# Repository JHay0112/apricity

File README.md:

# Apricity - Sunrise Alarm

Apricity is my second attempt at designing and building a sunrise alarm. 

The first attempt (https://jordanhay.com/blog/2021/08/sunrise-alarm) was based upon a development board and a 3D printed enclosure. Apricity will improve upon this design with a custom PCB and firmware.

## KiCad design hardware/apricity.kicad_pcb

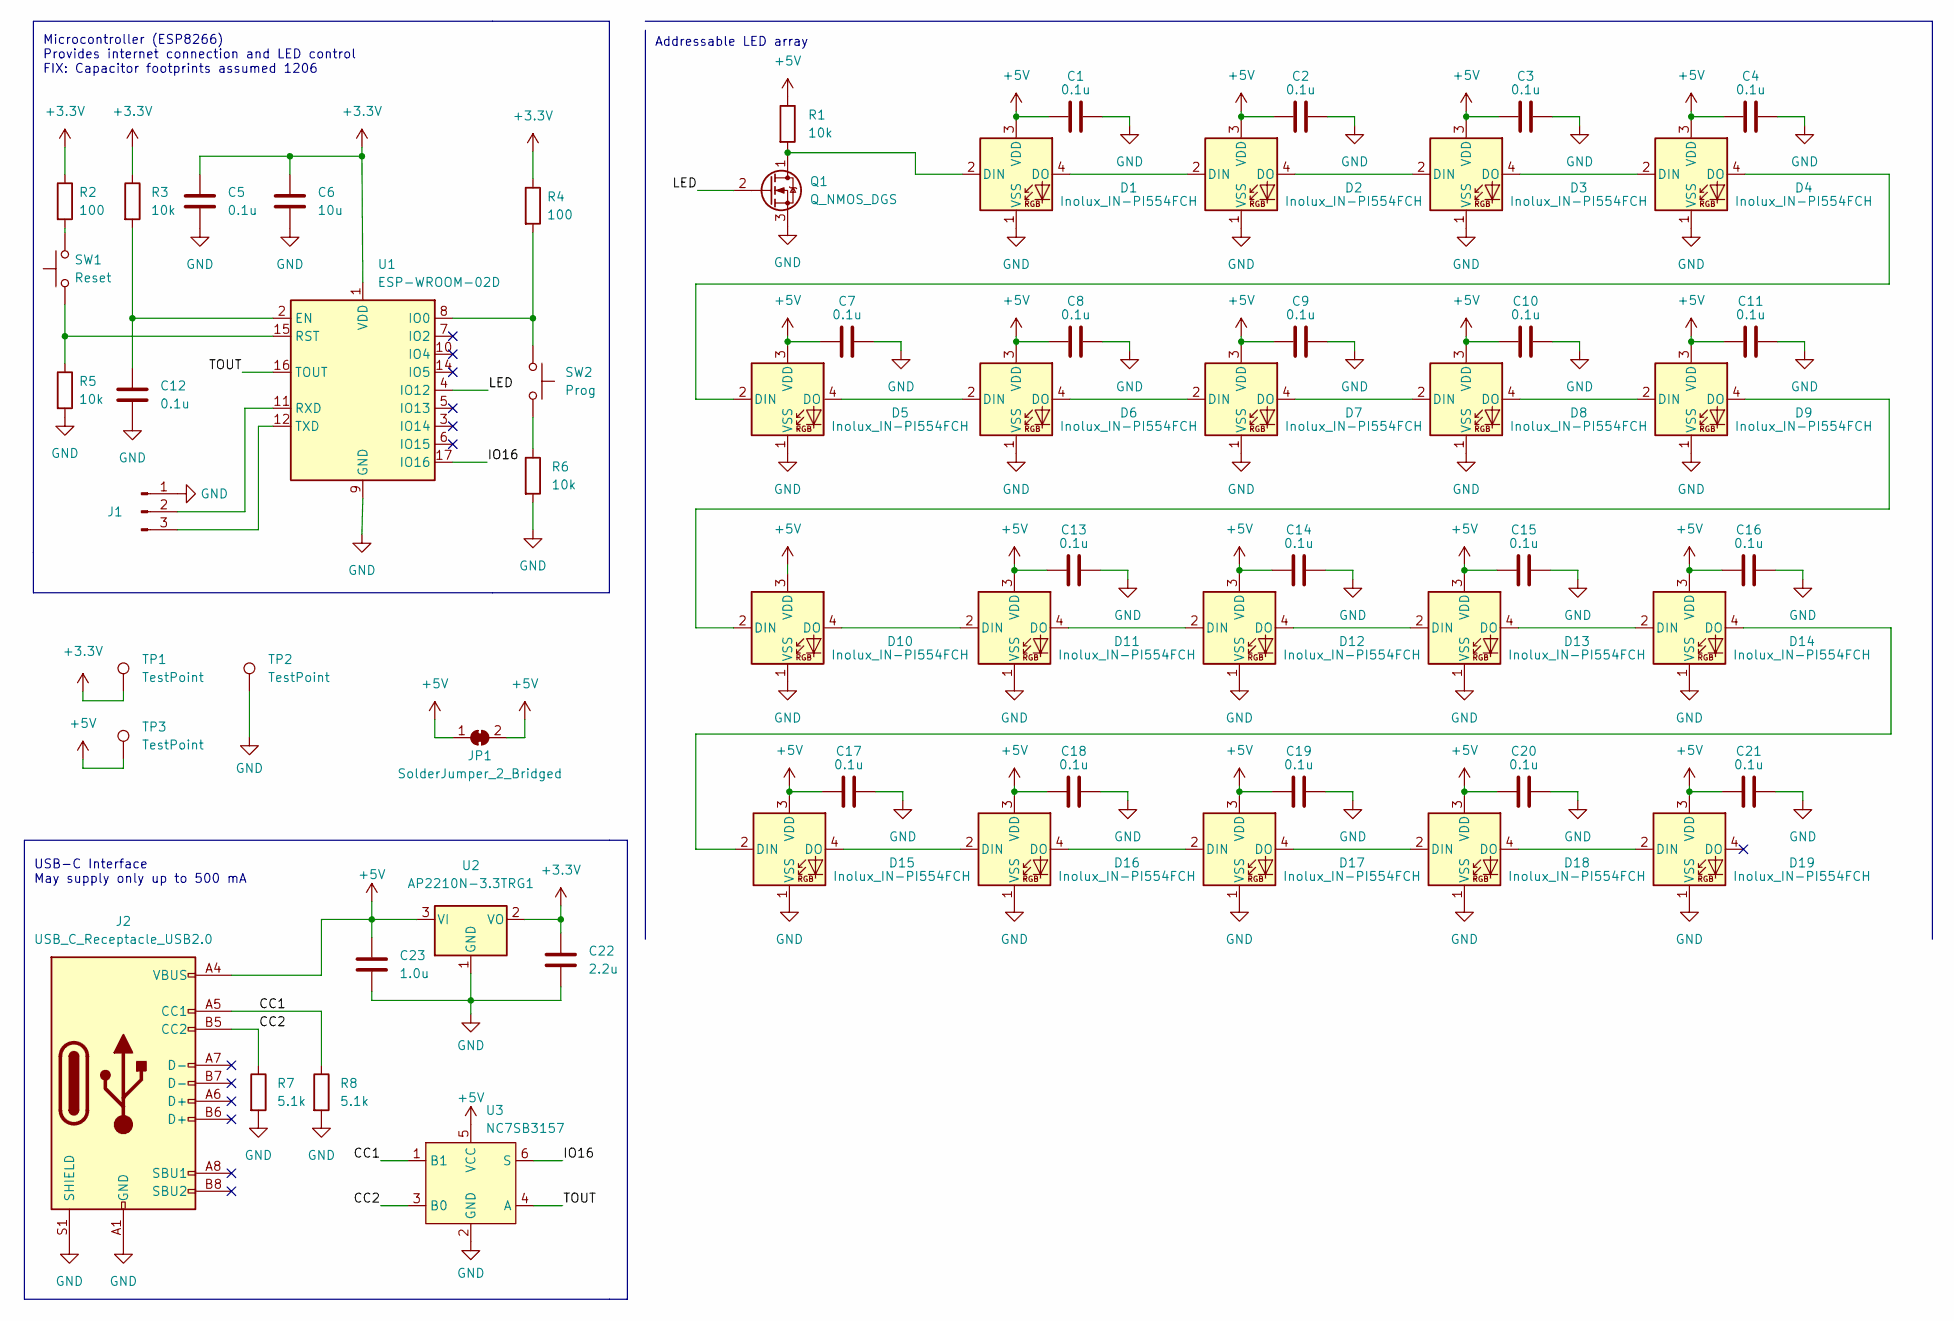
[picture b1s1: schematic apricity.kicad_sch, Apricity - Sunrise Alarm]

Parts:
C1, C2, C3, C4, C5, C7, C8, C9, C10, C11, C12, C13, C14, C15, C16, C17, C18, C19, C20, C21: 0.1u; C_1206_3216Metric_Pad1.33x1.80mm_HandSolder
C6: 10u; C_1206_3216Metric_Pad1.33x1.80mm_HandSolder
C22: 2.2u; C_1206_3216Metric_Pad1.33x1.80mm_HandSolder
C23: 1.0u; C_1206_3216Metric_Pad1.33x1.80mm_HandSolder
D1, D2, D3, D4, D5, D6, D7, D8, D9, D10, D11, D12, D13, D14, D15, D16, D17, D18, D19: Inolux_IN-PI554FCH; LED_Inolux_IN-PI554FCH_PLCC4_5.0x5.0mm_P3.2mm
J1: Conn_01x03_Male; PinHeader_1x03_P2.54mm_Horizontal
J2: USB_C_Receptacle_USB2.0; USB_C_Receptacle_Palconn_UTC16-G
JP1: SolderJumper_2_Bridged; R_0805_2012Metric_Pad1.20x1.40mm_HandSolder
Q1: Q_NMOS_DGS; TSOT-23_HandSoldering
R1, R3, R5, R6: 10k; R_0805_2012Metric_Pad1.20x1.40mm_HandSolder
R2, R4: 100; R_0805_2012Metric_Pad1.20x1.40mm_HandSolder
R7, R8: 5.1k; R_0805_2012Metric_Pad1.20x1.40mm_HandSolder
SW1: Reset; SW_SPST_CK_RS282G05A3
SW2: Prog; SW_SPST_CK_RS282G05A3
TP1, TP2, TP3: TestPoint; TestPoint_Pad_D1.0mm
U1: ESP-WROOM-02D; ESP-WROOM-02
U2: AP2210N-3.3TRG1; SOT-23_Handsoldering
U3: NC7SB3157; SOT-363_SC-70-6_Handsoldering

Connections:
+3.3V: C5.1, C6.1, C22.1, R2.1, R3.1, R4.1, TP1.1, U1.1 (VDD), U2.2 (VO)
+5V: C1.1, C2.1, C3.1, C4.1, C7.1, C8.1, C9.1, C10.1, C11.1, C13.1, C14.1, C15.1, C16.1, C17.1, C18.1, C19.1, C20.1, C21.1, C23.1, D1.3 (VDD), D2.3 (VDD), D3.3 (VDD), D4.3 (VDD), D5.3 (VDD), D6.3 (VDD), D7.3 (VDD), D8.3 (VDD), D9.3 (VDD), D10.3 (VDD), D11.3 (VDD), D12.3 (VDD), D13.3 (VDD), D14.3 (VDD), D15.3 (VDD), D16.3 (VDD), D17.3 (VDD), D18.3 (VDD), D19.3 (VDD), J2.A4 (VBUS), J2.A9 (VBUS), J2.B4 (VBUS), J2.B9 (VBUS), JP1.1 (A), JP1.2 (B), R1.1, TP3.1, U2.3 (VI), U3.5 (VCC)
/CC1: J2.A5 (CC1), R8.1, U3.1 (B1)
/CC2: J2.B5 (CC2), R7.1, U3.3 (B0)
/IO16: U1.17 (IO16), U3.6 (S)
/LED: Q1.2 (G), U1.4 (IO12)
/TOUT: U1.16 (TOUT), U3.4 (A)
GND: C1.2, C2.2, C3.2, C4.2, C5.2, C6.2, C7.2, C8.2, C9.2, C10.2, C11.2, C12.2, C13.2, C14.2, C15.2, C16.2, C17.2, C18.2, C19.2, C20.2, C21.2, C22.2, C23.2, D1.1 (VSS), D2.1 (VSS), D3.1 (VSS), D4.1 (VSS), D5.1 (VSS), D6.1 (VSS), D7.1 (VSS), D8.1 (VSS), D9.1 (VSS), D10.1 (VSS), D11.1 (VSS), D12.1 (VSS), D13.1 (VSS), D14.1 (VSS), D15.1 (VSS), D16.1 (VSS), D17.1 (VSS), D18.1 (VSS), D19.1 (VSS), J1.1, J2.A1 (GND), J2.A12 (GND), J2.B1 (GND), J2.B12 (GND), J2.S1 (SHIELD), Q1.3 (S), R5.2, R6.2, R7.2, R8.2, TP2.1, U1.9 (GND), U1.13 (GND), U1.18 (GND), U1.19 (GND), U2.1 (GND), U3.2 (GND)
unnamed: C12.1, R3.2, U1.2 (EN)
unnamed: D1.2 (DIN), Q1.1 (D), R1.2
unnamed: D1.4 (DO), D2.2 (DIN)
unnamed: D2.4 (DO), D3.2 (DIN)
unnamed: D3.4 (DO), D4.2 (DIN)
unnamed: D4.4 (DO), D5.2 (DIN)
unnamed: D5.4 (DO), D6.2 (DIN)
unnamed: D6.4 (DO), D7.2 (DIN)
unnamed: D7.4 (DO), D8.2 (DIN)
unnamed: D8.4 (DO), D9.2 (DIN)
unnamed: D9.4 (DO), D10.2 (DIN)
unnamed: D10.4 (DO), D11.2 (DIN)
unnamed: D11.4 (DO), D12.2 (DIN)
unnamed: D12.4 (DO), D13.2 (DIN)
unnamed: D13.4 (DO), D14.2 (DIN)
unnamed: D14.4 (DO), D15.2 (DIN)
unnamed: D15.4 (DO), D16.2 (DIN)
unnamed: D16.4 (DO), D17.2 (DIN)
unnamed: D17.4 (DO), D18.2 (DIN)
unnamed: D18.4 (DO), D19.2 (DIN)
unnamed: J1.2, U1.11 (RXD)
unnamed: J1.3, U1.12 (TXD)
unnamed: R2.2, SW1.2
unnamed: R4.2, SW2.1, U1.8 (IO0)
unnamed: R5.1, SW1.1, U1.15 (RST)
unnamed: R6.1, SW2.2

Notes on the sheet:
Addressable LED array
USB-C Interface May supply only up to 500 mA
Microcontroller (ESP8266) Provides internet connection and LED control FIX: Capacitor footprints assumed 1206

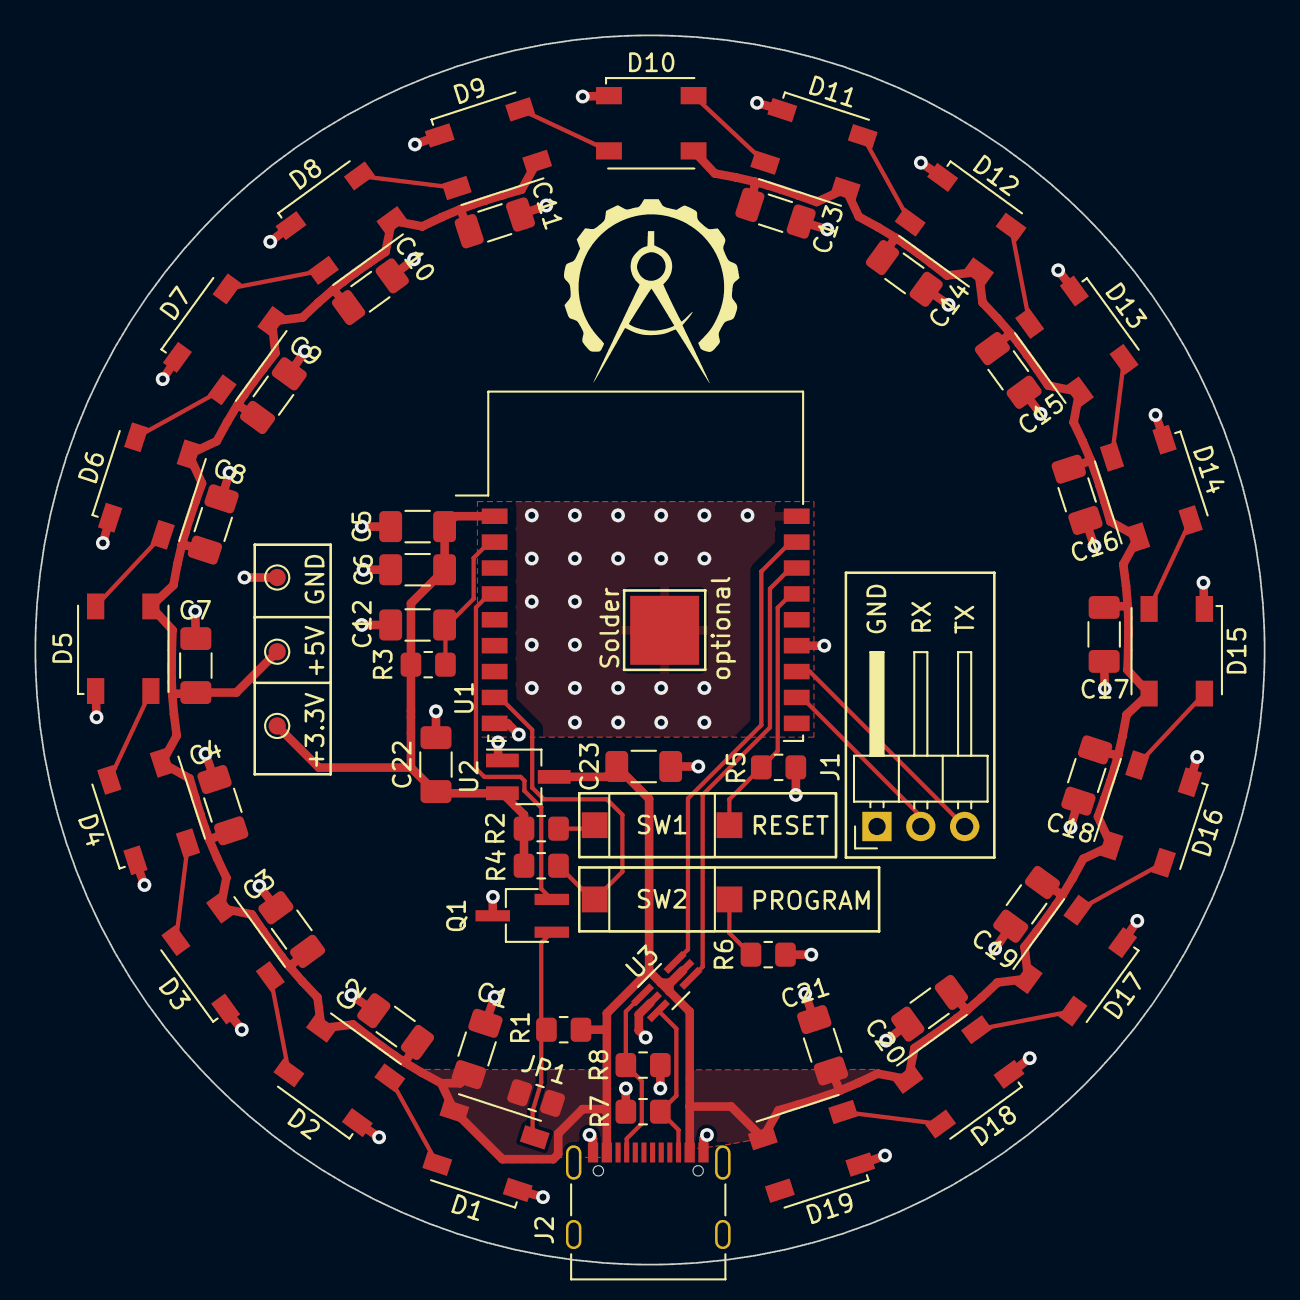
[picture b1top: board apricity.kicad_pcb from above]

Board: 2 copper layers, 71.2 x 71.2 mm, 62 parts (0 on the bottom side), 34 nets.

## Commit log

2022-12-11 Setup hardware and readme
2022-12-14 Prototype ESP8266-based version
2022-12-24 lay down prototype circular array
2022-12-24 Ignore auto saved files
2022-12-24 Perform component relink and add attribution
2022-12-24 Experiment with power plane
2022-12-24 Refine keepouts for power plane
2022-12-27 fix power plane and add room for components
2022-12-27 Annotate schematic and add power components
2022-12-27 layout power components on pcb
2022-12-27 Play with power planes
2022-12-28 re-arrange power components
2022-12-28 remove vias from under pads
2022-12-28 reintroduce ground plane below controller
2022-12-28 circular power plane cutout
2022-12-28 remove led vias from pads
2022-12-28 reduce power 'trace' width
2022-12-28 remove loops
2022-12-28 use jumper to connect power trace
2022-12-28 fix routing issues with jumper
2022-12-29 flesh out power regulation
2022-12-29 refine power as per esp datasheet
2022-12-29 add peripherals for programming
2022-12-29 add boot mode in schematic
2022-12-29 add logo on back of pcb
2022-12-29 add buttons for program and reset
2022-12-29 rearrange for silkscreen consistency
2022-12-29 switch to horizontal programmer
2022-12-29 fix drc errors
2022-12-29 improve rx/tx symmetry
2022-12-29 capitalize button labels
2022-12-29 replace zones with traces
2022-12-29 add capacitors for LEDs
2022-12-29 add back in capacitor for D1
2022-12-31 add power test points
2023-01-01 tweak test point positions
2023-01-01 make room for usb c controller
2023-01-03 add analogue switch for checking current supply
2023-01-03 tweak silkscreen and connector placement
2023-01-03 tweak led power planes
2023-01-03 ignore generated step files
2023-01-03 tweak pads again, add thermal reliefs where useful
2023-01-04 add placeholder logic level shifting
